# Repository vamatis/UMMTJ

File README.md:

# UMMTJ (Universal Midscale Manufacturing Test Jig)

The UMMTJ (Universal Midscale Manufacturing Test Jig) is an open source programmer and test jig design designed to simplify the life of small electronic manufacturing companies and prototypists.

By defining hardware an software standards, it aims at making automated programming and testing of boards or panels cheap and easy. Along with the jig itself, the project will also include all the SDKs designed to operate the whole system. 

The ultimate goal is to be a turn-key solution with hardware, software and processes to simplify the design, build and use of a production-ready prog and test jig.

**Please [read the wiki here](https://github.com/vamatis/UMMTJ/wiki)!** The wiki covers information about all the design considerations, the state of the project, contributing instructions, and frequently asked questions.

Exported versions of the sources (STLs, schematic PDFs, compiled binaries, etc) can fbe found attached to the [latest release](https://github.com/vamatis/UMMTJ/releases).

## Project Goals:
The main project goals are as follow:

	- As much as possible, every part should be designed in a way to facilitate acces/modification by using open source tools
	- In the end, as much as the "automatable" stuff should be
	- If a standard is already in place, it should be followed if possible
	- Jig must be usable standalone (with an integrated single board computer) or as a "slave" for prototyping or debugging

There are multiple parts that I hope will be covered by the project in the end, to make it a real turn-key solution. The two main categories would be hardware and software.

### Hardware:

	- Design and build of the main frame for the jig
	PCB target dimmensions are 230x230mm to be able to run bigger boards or even small panels 
	As many of the shelf parts should be used, and the jig must be buildable without too much tools or experience
	- Design and build of the electronic boards to let the magic happen
	Most of the complexity should reside in the mainboard of the system, leaving "per-board" adapters to be as simple and cheap as possible
	As many use cases as practically viable should be taken into account

### Software:
	- KiCad plugin to automate the generation of the "per-board" adapters as much as possible
	- Firmware to run on the onboard microcontroller
	- SDK / application examples of the control software side, which operates the jig

	--> using https://github.com/snhobbs/kicad-parts-placer and https://github.com/snhobbs/kicad-testpoints-pcm ?

## How do I get one?

As this project is at the very beginning, the only way to get one is to build it yourself using the BOM and Gerbers in the release pages. In the future, I hope to be able to sell kits for the system, as well as the individual parts.

## Contributing

As it might show, I'm not really an expert on the subject (on anything actually), so help is very welcome! If you would like to contribute to the project, Check out the [contributing page](https://github.com/vamatis/UMMTJ/wiki/contributing) to get started.

## Community

Discussion about the project happens on the [Discord server](https://discord.com/invite/uQHQamh2w4)!

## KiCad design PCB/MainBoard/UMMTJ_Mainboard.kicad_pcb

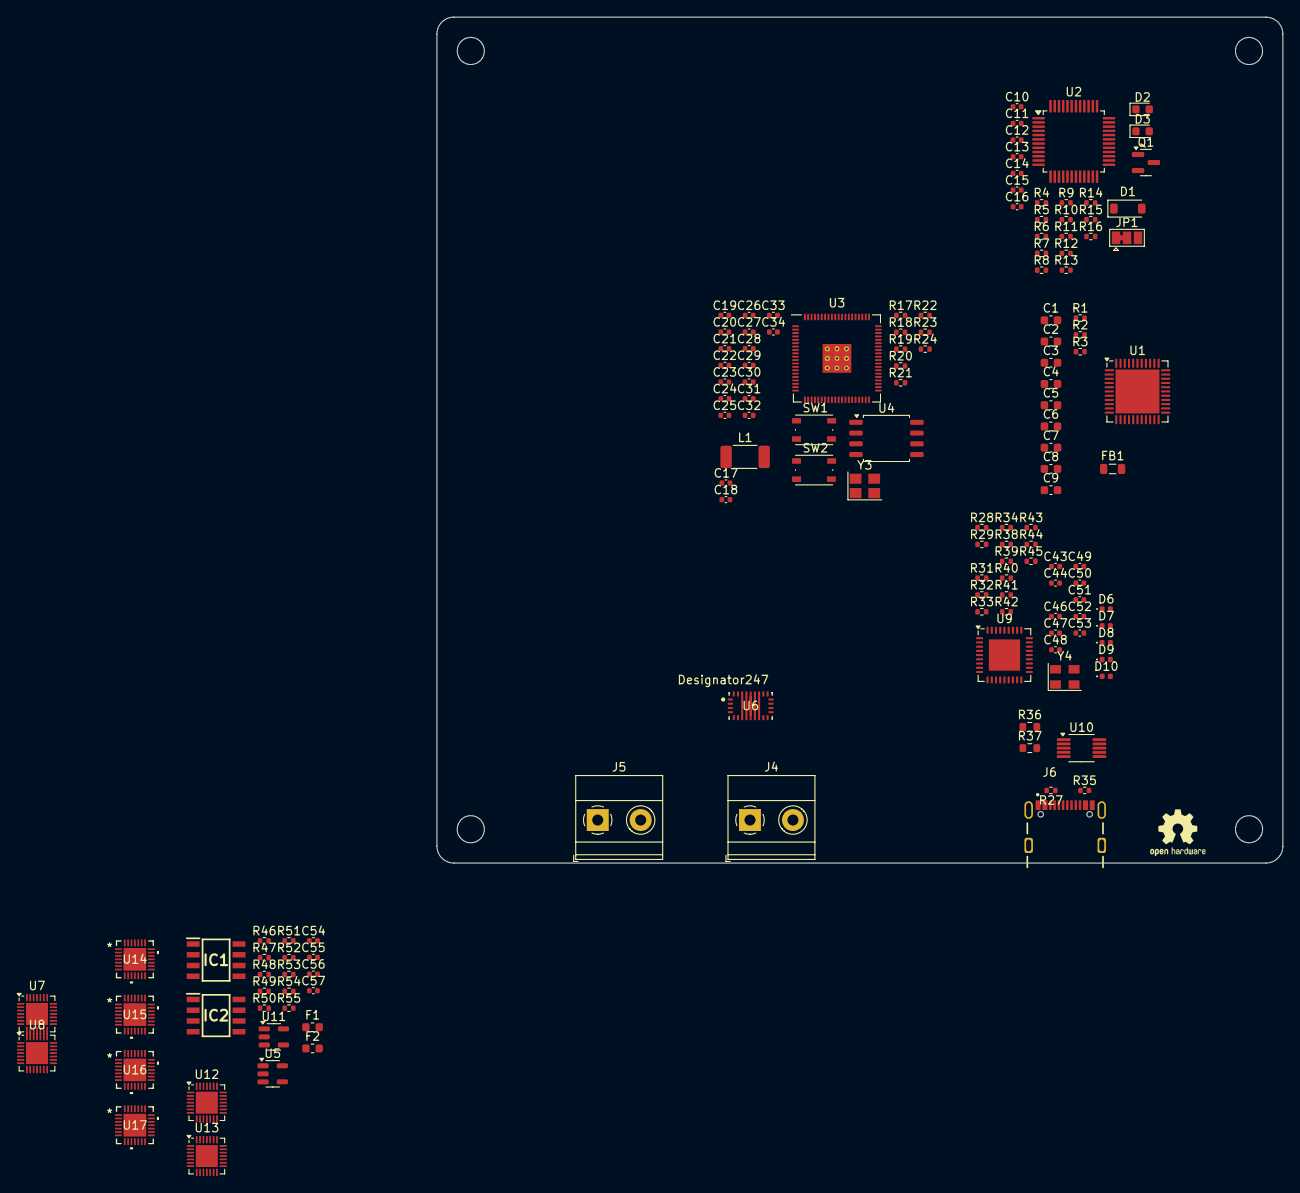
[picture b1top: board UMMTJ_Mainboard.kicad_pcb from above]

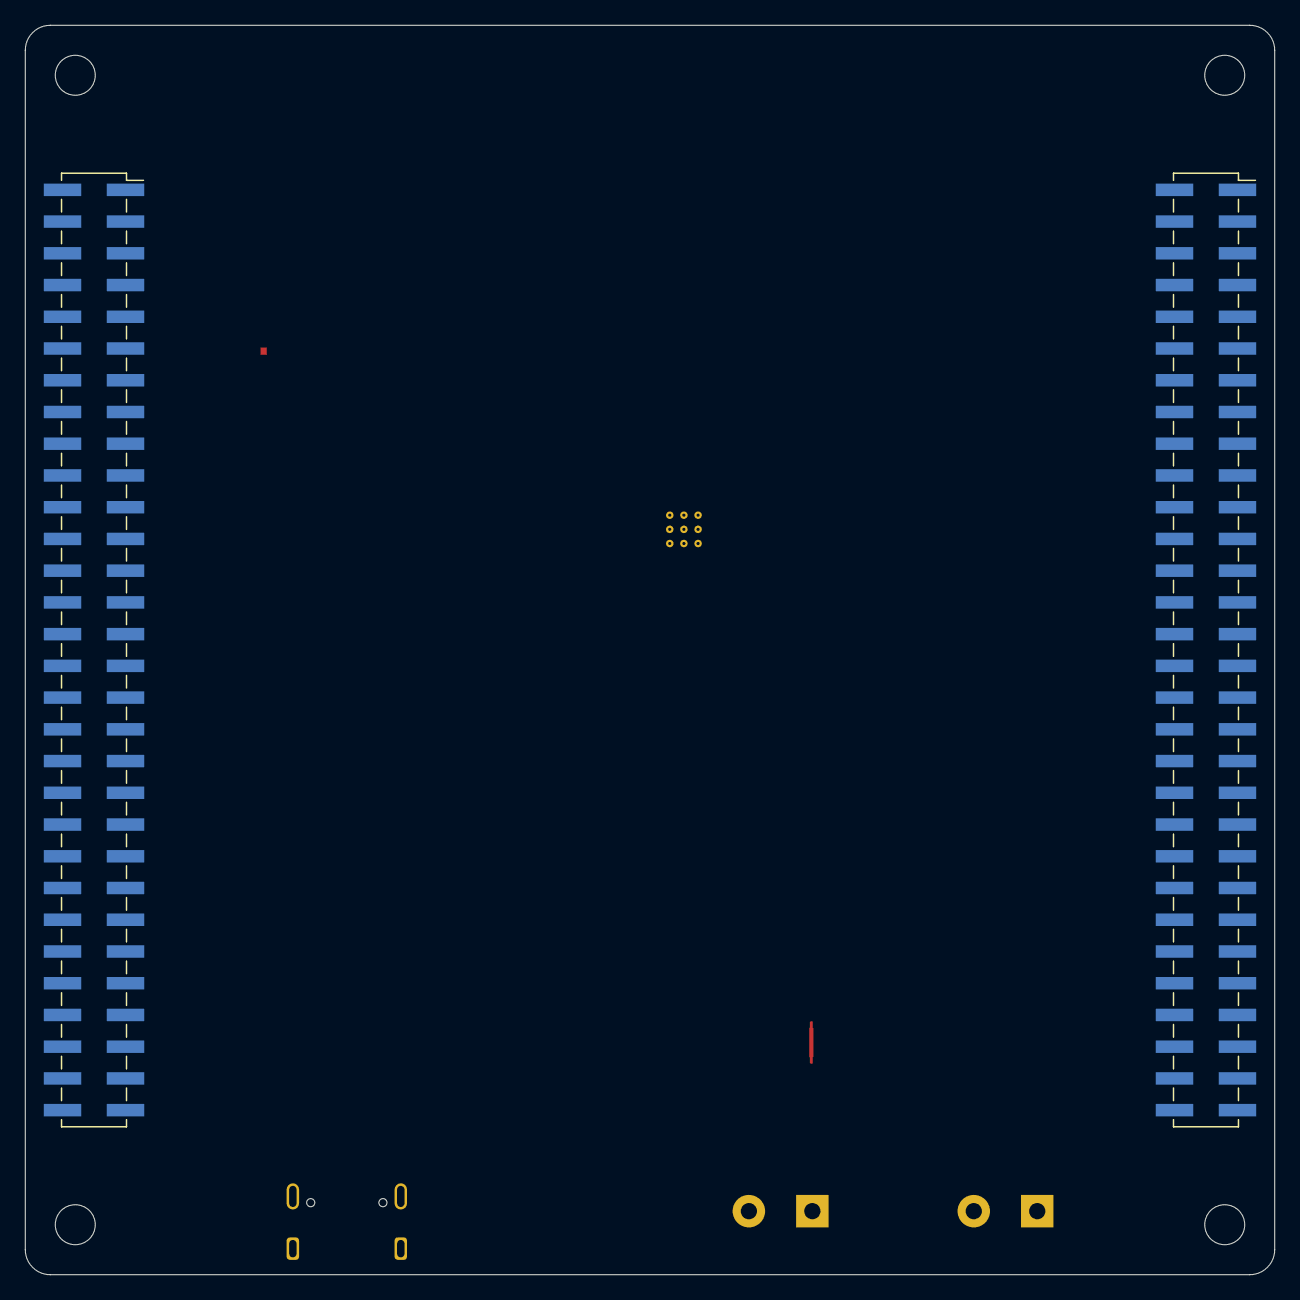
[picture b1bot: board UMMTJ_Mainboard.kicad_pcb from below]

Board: 4 copper layers, 100.0 x 100.0 mm, 146 parts (2 on the bottom side), 81 nets, no tracks yet.

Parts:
C1, C7, C9: 1uF; C_0603_1608Metric
C2, C3, C4, C8: 100nF; C_0603_1608Metric
C5, C6: C; C_0603_1608Metric
C10, C13, C14, C15, C16, C46, C47, C48, C49, C50, C51, C52: 100nF; C_0402_1005Metric
C11, C12: 20pF; C_0402_1005Metric
C17, C18, C20: 4.7u; C_0402_1005Metric
C19, C22, C23, C24, C25, C26, C27, C28, C29, C30, C31, C34: 100n; C_0402_1005Metric
C21, C53: 4.7uF; C_0402_1005Metric
C32, C33: 15p; C_0402_1005Metric
C43, C44: 30pF; C_0402_1005Metric
C54, C55, C56, C57: C; C_0402_1005Metric
D1: B5819W; D_SOD-123
D2: BLUE; LED_0603_1608Metric
D3: RED; LED_0603_1608Metric
D6, D7, D8, D9, D10: IN-S42BT5G; LED_0402_1005Metric
F1, F2: Fuse; Fuse_0603_1608Metric
FB1: MH2029-300Y; L_0805_2012Metric
H1, H2, H3, H4: MountingHole; MountingHole_3.2mm_M3
IC1, IC2: LT1910ES8#PBF; SOIC127P599X175-8N
J1: Power; PinSocket_2x30_P2.54mm_Vertical_SMD
J2: GPIOS; PinSocket_2x30_P2.54mm_Vertical_SMD
J4: Main Power; TerminalBlock_Phoenix_MKDS-1,5-2-5.08_1x02_P5.08mm_Horizont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
J5: External Supply; TerminalBlock_Phoenix_MKDS-1,5-2-5.08_1x02_P5.08mm_Horizont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
J6: USB4105-GF-A; GCT_USB4105-GF-A
JP1: SolderJumper-3_P1.3mm_Bridged12_Pad1.0x1.5mm
L1: 3.3u; L_2010_5025Metric
Q1: S9013; SOT-23
R1, R2: 22R; R_0402_1005Metric
R3, R7, R8: 10k; R_0402_1005Metric
R4, R5, R28, R29, R32, R33, R38, R39, R42, R43: 100k; R_0402_1005Metric
R6: 1K5; R_0402_1005Metric
R9: 39k; R_0402_1005Metric
R10: DNP; R_0402_1005Metric
R11, R12: 100R; R_0402_1005Metric
R13, R14: 4k7; R_0402_1005Metric
R15, R16: 220R; R_0402_1005Metric
R17, R19, R24, R31, R40, R41, R44, R45: 1k; R_0402_1005Metric
R18: 33; R_0402_1005Metric
R20, R21: 27; R_0402_1005Metric
R22: 0; R_0402_1005Metric
R23: DNF; R_0402_1005Metric
R27, R35: 5,1k; R_0402_1005Metric
R34: 12k 1%; R_0402_1005Metric
R36, R37: 2,2k 1%; R_0603_1608Metric
R46, R47, R48, R49, R50, R51, R52, R53, R54, R55: R; R_0402_1005Metric
SW1, SW2: SW_Push; SW_Push_1P1T_NO_Vertical_Wuerth_434133025816
U1: ATmega32U4-M; QFN-44-1EP_7x7mm_P0.5mm_EP5.2x5.2mm
U2: STM32F103CB; LQFP-48_7x7mm_P0.5mm
U3: RP2350_80QFN; RP2350-QFN-80-1EP_10x10_P0.4mm_EP3.4x3.4mm_ThermalVias
U4: W25Q128JVS; SOIC-8_5.23x5.23mm_P1.27mm
U5, U11: INA138; SOT-23-5
U6: TPS55289
U7, U8, U12, U13: MAX14662; QFN-28-1EP_4x4mm_P0.4mm_EP2.6x2.6mm
U9: USB2514B-I/M2; QFN-36-1EP_6x6mm_P0.5mm_EP3.7x3.7mm
U10: FSUSB42MUX; MSOP-10_3x3mm_P0.5mm
U14, U15, U16, U17: MAX14661ETI+; 21-0139I_T2844-1_MXM
Y3: ABM8-272-T3; Crystal_SMD_3225-4Pin_3.2x2.5mm
Y4: ECS-240-20-33-TR3; Crystal_SMD_EuroQuartz_MT-4Pin_3.2x2.5mm

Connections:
+1V1: C18.1, C19.1, C21.1, C22.1, L1.1, U3.10 (DVDD), U3.32 (DVDD), U3.51 (DVDD), U3.65 (VREG_FB)
+3V3: C13.1, C14.1, C15.1, C16.1, C17.1, C23.1, C24.1, C25.1, C26.1, C27.1, C28.1, C29.1, C30.1, C31.1, C34.1, JP1.1 (A), Q1.3 (C), R4.2, R15.2, R18.1, R23.1, U2.1 (VBAT), U2.9 (VDDA), U2.24 (VDD), U2.36 (VDD), U2.48 (VDD), U3.5 (IOVDD), U3.15 (IOVDD), U3.24 (IOVDD), U3.29 (IOVDD), U3.41 (IOVDD), U3.50 (IOVDD), U3.59 (ADC_AVDD), U3.60 (IOVDD), U3.64 (VREG_VIN), U3.68 (USB_OTP_VDD), U3.69 (QSPI_IOVDD), U3.76 (IOVDD), U4.8 (VCC), U10.1 (VCC)
+5V: D1.1 (K), R8.2
/AVR Programmer/AVR_Prog_3V3: C1.1, C2.1, C4.1, C8.1, FB1.1, R3.1, U1.2 (UVCC), U1.7 (VBUS), U1.14 (VCC), U1.34 (VCC)
/Main Controller/FLASH_SS: R22.2, R23.2, U4.1 (~CS)
/Main Controller/QSPI_SCLK: U3.71 (QSPI_SCLK), U4.6 (CLK)
/Main Controller/QSPI_SD0: U3.72 (QSPI_SD0), U4.5 (DI(IO0))
/Main Controller/QSPI_SD1: U3.74 (QSPI_SD1), U4.2 (DO(IO1))
/Main Controller/QSPI_SD2: U3.73 (QSPI_SD2), U4.3 (IO2)
/Main Controller/QSPI_SD3: U3.70 (QSPI_SD3), U4.7 (IO3)
/Main Controller/QSPI_SS: R19.1, R22.1, U3.75 (QSPI_SS)
/Main Controller/RUN: SW2.2, U3.35 (RUN)
/Main Controller/VREG_AVDD: C20.1, R18.2, U3.61 (VREG_AVDD)
/Main Controller/VREG_LX: L1.2, U3.63 (VREG_LX)
/Main Controller/XIN: C32.1, U3.30 (XIN), Y3.1
/Main Controller/XOUT: R24.1, U3.31 (XOUT)
/Main Controller/~USB_BOOT: R19.2, SW1.2
/USB/SEL_ENABLE: J6.A4_B9 (VBUS), J6.B4_A9 (VBUS), R36.1
/USB/SLAVE_D+: J6.A6 (DP1), J6.B6 (DP2), U10.7 (HSD1+)
/USB/SLAVE_D-: J6.A7 (DN1), J6.B7 (DN2), U10.6 (HSD1-)
B0: R5.2, U2.44 (BOOT0)
D+: R6.1, U2.33 (PA12), U10.9 (HSD2+)
D-: U2.32 (PA11), U10.8 (HSD2-)
GND: C1.2, C2.2, C3.2, C4.2, C5.2, C6.1, C7.2, C8.2, C9.2, C10.2, C11.2, C12.2, C13.2, C14.2, C15.2, C16.2, C17.2, C18.2, C19.2, C20.2, C21.2, C22.2, C23.2, C24.2, C25.2, C26.2, C27.2, C28.2, C29.2, C30.2, C31.2, C32.2, C33.2, C34.2, C43.1, C44.1, C46.2, C47.2, C48.2, C49.2, C50.2, C51.2, C52.2, C53.2, D6.1 (K), D7.1 (K), D8.1 (K), D9.1 (K), D10.1 (K), J6.A1_B12 (GND), J6.B1_A12 (GND), J6.SH1 (SHELL_GND), J6.SH2 (SHELL_GND), J6.SH3 (SHELL_GND), J6.SH4 (SHELL_GND), R5.1, R7.1, R9.1, R10.1, R14.1, R16.1, R17.2, R27.2, R33.2, R34.2, R35.2, R37.2, R38.2, R39.2, R42.2, R43.2, SW1.1, U1.5 (UGND), U1.15 (GND), U1.23 (GND), U1.35 (GND), U1.43 (GND), U1.45 (GND), U2.8 (VSSA), U2.23 (VSS), U2.35 (VSS), U2.47 (VSS), U3.62 (VREG_PGND), U3.81 (GND), U4.4 (GND), U9.37 (VSS), U10.5 (GND), U10.10 (~OE), Y3.2, Y3.4, Y4.2, Y4.4
LED: D2.1 (K), D3.2 (A), U2.30 (PA9)
unnamed: C9.1, FB1.2, U1.24 (AVCC), U1.44 (AVCC)
unnamed: C33.1, R24.2, Y3.3
unnamed: D2.2 (A), R15.1
unnamed: D3.1 (K), R16.2
unnamed: D6.2 (A), R31.2
unnamed: D7.2 (A), R40.1
unnamed: D8.2 (A), R41.1
unnamed: D9.2 (A), R44.1
unnamed: D10.2 (A), R45.1
unnamed: IC1.5 (GATE), R48.1
unnamed: IC1.6 (SENSE), R49.2
unnamed: IC2.5 (GATE), R53.1
unnamed: IC2.6 (SENSE), R52.2
unnamed: J6.A5 (CC1), R27.1
unnamed: J6.B5 (CC2), R35.1
unnamed: JP1.2 (C), R13.2
unnamed: Q1.1 (B), R8.1, R9.2, R11.2
unnamed: Q1.2 (E), R6.2
unnamed: R17.1, SW2.1
unnamed: C3.1, U1.42 (AREF)
unnamed: R1.2, U1.4 (D+)
unnamed: R2.2, U1.3 (D-)
unnamed: C7.1, U1.6 (UCAP)
unnamed: C5.1, U1.17 (XTAL1)
unnamed: C6.2, U1.16 (XTAL2)
unnamed: R3.2, U1.13 (~RESET)
unnamed: C10.1, R4.1, U2.7 (NRST)
unnamed: R13.1, R14.2, U2.10 (PA0)
unnamed: R12.1, U2.25 (PB12)
unnamed: R7.2, U2.2 (PC13)
unnamed: R10.2, U2.3 (PC14)
unnamed: C11.1, U2.5 (PD0)
unnamed: C12.1, U2.6 (PD1)
unnamed: R21.2, U3.66 (USB_DM)
unnamed: R20.2, U3.67 (USB_DP)
unnamed: U7.11 (GND), U7.25 (GND), U7.29 (GND)
unnamed: U8.11 (GND), U8.25 (GND), U8.29 (GND)
unnamed: C48.1, U9.14 (CRFILT)
unnamed: C47.1, U9.34 (PLLFILT)
unnamed: R42.1, R44.2, U9.12 (PRTPWR1/BC_EN1)
unnamed: R38.1, R40.2, U9.16 (PRTPWR2/BC_EN2)
unnamed: R43.1, R45.2, U9.18 (PRTPWR3/BC_EN3)
unnamed: R39.1, R41.2, U9.20 (PRTPWR4/BC_EN4)
unnamed: R34.1, U9.35 (RBIAS)
unnamed: C46.1, R32.2, U9.26 (RESET_N)
unnamed: R31.1, R33.1, U9.28 (SUSP_IND/LOCAL_PWR/NON_REM0)
unnamed: R29.1, U9.27 (VBUS_DET)
unnamed: C43.2, R28.1, U9.33 (XTALIN/CLKIN), Y4.3
unnamed: C44.2, R28.2, U9.32 (XTALOUT), Y4.1
unnamed: R36.2, R37.1, U10.2 (SEL)
unnamed: U12.11 (GND), U12.25 (GND), U12.29 (GND)
unnamed: U13.11 (GND), U13.25 (GND), U13.29 (GND)
RENUM: R11.1, U2.38 (PA15)
T_CLK: U2.15 (PA5), U2.26 (PB13)
T_DIO: R12.2, U2.27 (PB14)
VCC: C49.1, C50.1, C51.1, C52.1, C53.1, R29.2, R32.1, U9.5 (VDDA33), U9.10 (VDDA33), U9.15 (VDD33), U9.23 (VDD33), U9.29 (VDDA33), U9.36 (VDDA33)

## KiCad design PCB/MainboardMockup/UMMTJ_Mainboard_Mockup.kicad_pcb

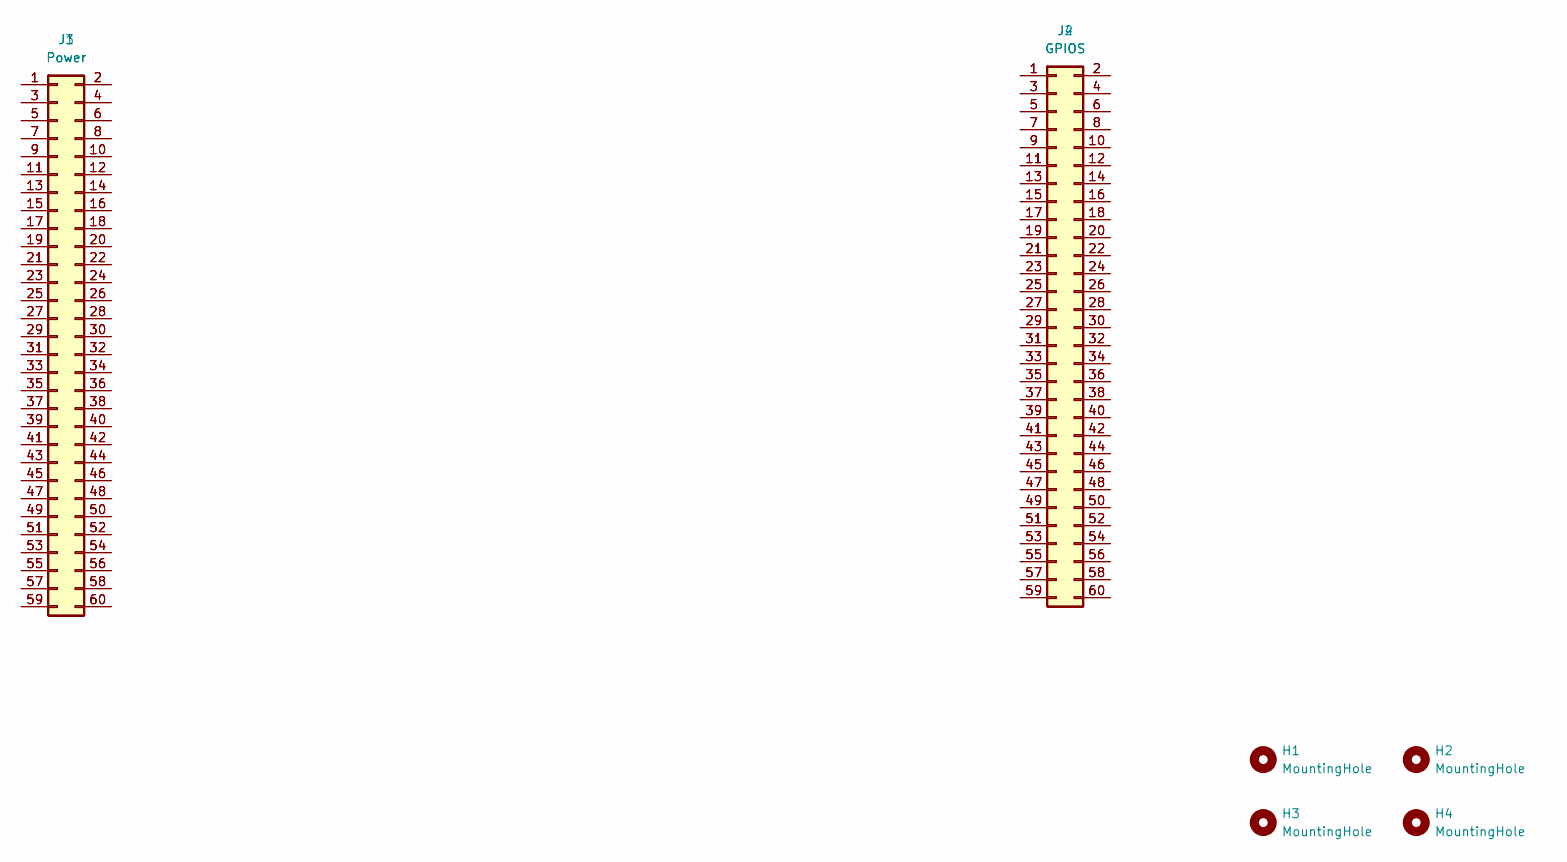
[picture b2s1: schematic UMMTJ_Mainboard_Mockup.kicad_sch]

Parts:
H1, H2, H3, H4: MountingHole; MountingHole_3.2mm_M3
J1: Power; PinSocket_2x30_P2.54mm_Vertical_SMD
J2: GPIOS; PinSocket_2x30_P2.54mm_Vertical_SMD
J3: Power; PinHeader_2x30_P2.54mm_Vertical
J4: GPIOS; PinHeader_2x30_P2.54mm_Vertical

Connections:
unnamed: J1.1, J3.1
unnamed: J1.2, J3.2
unnamed: J1.3, J3.3
unnamed: J1.4, J3.4
unnamed: J1.5, J3.5
unnamed: J1.6, J3.6
unnamed: J1.7, J3.7
unnamed: J1.8, J3.8
unnamed: J1.9, J3.9
unnamed: J1.10, J3.10
unnamed: J1.11, J3.11
unnamed: J1.12, J3.12
unnamed: J1.13, J3.13
unnamed: J1.14, J3.14
unnamed: J1.15, J3.15
unnamed: J1.16, J3.16
unnamed: J1.17, J3.17
unnamed: J1.18, J3.18
unnamed: J1.19, J3.19
unnamed: J1.20, J3.20
unnamed: J1.21, J3.21
unnamed: J1.22, J3.22
unnamed: J1.23, J3.23
unnamed: J1.24, J3.24
unnamed: J1.25, J3.25
unnamed: J1.26, J3.26
unnamed: J1.27, J3.27
unnamed: J1.28, J3.28
unnamed: J1.29, J3.29
unnamed: J1.30, J3.30
unnamed: J1.31, J3.31
unnamed: J1.32, J3.32
unnamed: J1.33, J3.33
unnamed: J1.34, J3.34
unnamed: J1.35, J3.35
unnamed: J1.36, J3.36
unnamed: J1.37, J3.37
unnamed: J1.38, J3.38
unnamed: J1.39, J3.39
unnamed: J1.40, J3.40
unnamed: J1.41, J3.41
unnamed: J1.42, J3.42
unnamed: J1.43, J3.43
unnamed: J1.44, J3.44
unnamed: J1.45, J3.45
unnamed: J1.46, J3.46
unnamed: J1.47, J3.47
unnamed: J1.48, J3.48
unnamed: J1.49, J3.49
unnamed: J1.50, J3.50
unnamed: J1.51, J3.51
unnamed: J1.52, J3.52
unnamed: J1.53, J3.53
unnamed: J1.54, J3.54
unnamed: J1.55, J3.55
unnamed: J1.56, J3.56
unnamed: J1.57, J3.57
unnamed: J1.58, J3.58
unnamed: J1.59, J3.59
unnamed: J1.60, J3.60
unnamed: J2.1, J4.1
unnamed: J2.2, J4.2
unnamed: J2.3, J4.3
unnamed: J2.4, J4.4
unnamed: J2.5, J4.5
unnamed: J2.6, J4.6
unnamed: J2.7, J4.7
unnamed: J2.8, J4.8
unnamed: J2.9, J4.9
unnamed: J2.10, J4.10
unnamed: J2.11, J4.11
unnamed: J2.12, J4.12
unnamed: J2.13, J4.13
unnamed: J2.14, J4.14
unnamed: J2.15, J4.15
unnamed: J2.16, J4.16
unnamed: J2.17, J4.17
unnamed: J2.18, J4.18
unnamed: J2.19, J4.19
unnamed: J2.20, J4.20
unnamed: J2.21, J4.21
unnamed: J2.22, J4.22
unnamed: J2.23, J4.23
unnamed: J2.24, J4.24
unnamed: J2.25, J4.25
unnamed: J2.26, J4.26
unnamed: J2.27, J4.27
unnamed: J2.28, J4.28
unnamed: J2.29, J4.29
unnamed: J2.30, J4.30
unnamed: J2.31, J4.31
unnamed: J2.32, J4.32
unnamed: J2.33, J4.33
unnamed: J2.34, J4.34
unnamed: J2.35, J4.35
unnamed: J2.36, J4.36
unnamed: J2.37, J4.37
unnamed: J2.38, J4.38
unnamed: J2.39, J4.39
unnamed: J2.40, J4.40
unnamed: J2.41, J4.41
unnamed: J2.42, J4.42
unnamed: J2.43, J4.43
unnamed: J2.44, J4.44
unnamed: J2.45, J4.45
unnamed: J2.46, J4.46
unnamed: J2.47, J4.47
unnamed: J2.48, J4.48
unnamed: J2.49, J4.49
unnamed: J2.50, J4.50
unnamed: J2.51, J4.51
unnamed: J2.52, J4.52
unnamed: J2.53, J4.53
unnamed: J2.54, J4.54
unnamed: J2.55, J4.55
unnamed: J2.56, J4.56
unnamed: J2.57, J4.57
unnamed: J2.58, J4.58
unnamed: J2.59, J4.59
unnamed: J2.60, J4.60

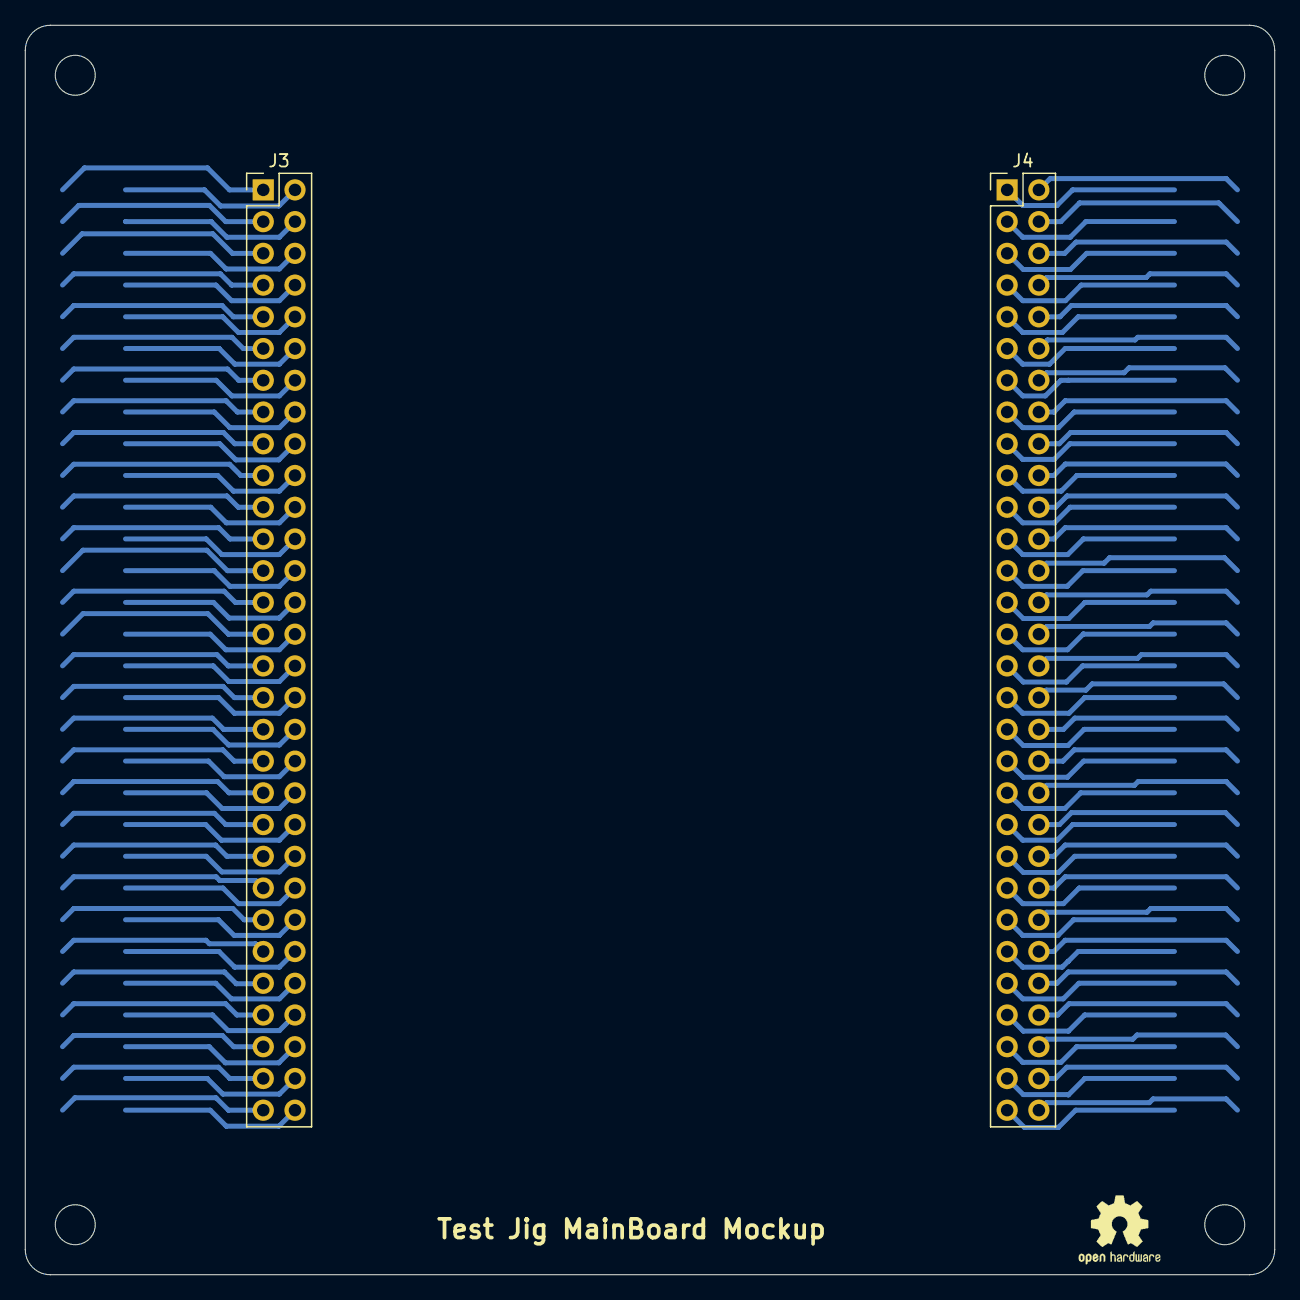
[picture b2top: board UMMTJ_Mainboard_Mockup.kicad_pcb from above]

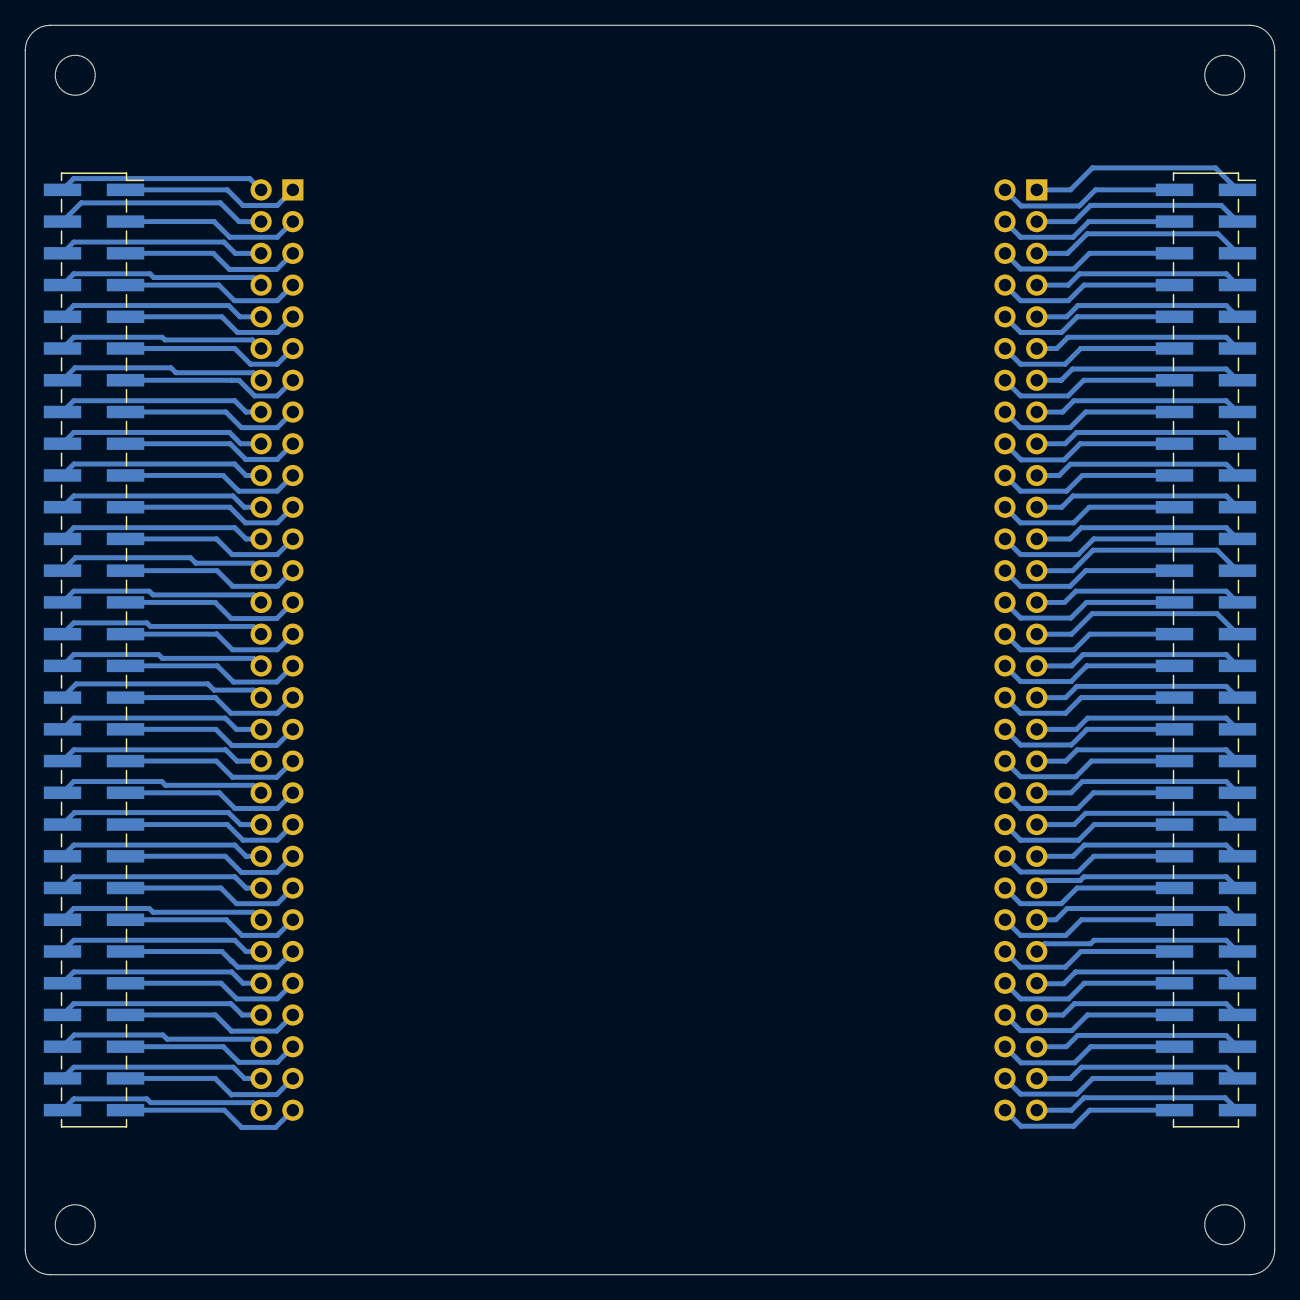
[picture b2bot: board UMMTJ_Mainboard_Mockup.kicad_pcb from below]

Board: 2 copper layers, 100.0 x 100.0 mm, 8 parts (2 on the bottom side), 120 nets.

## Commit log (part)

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2024-10-24 Started tests on Freecad for 1st frame Iteration. Added drawings for future wiki
2024-10-25 Working on Cad, slowly but surely(?)
2024-10-26 Moving forward with the CAD model
2024-10-26 added image for README page
2024-10-30 Starting the schematics
2024-11-14 Little update on the AVR Programmer, file logos
2024-12-05 Schematic in progress. Starting to finish each hier. page 1 by 1 now
2024-12-17 schematic progress
